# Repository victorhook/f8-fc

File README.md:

# f8 fc - Open source brushed x8 AIO

[f8 fc](https://github.com/victorhook/f8-fc) is a fully open source AIO flight controller that is made primarily for small drones with brushed drones. It features:
- STM32F405 microcontroller with 1MB flash
- BMI270 imu
- BMP388 barometer
- Onboard 16MB external flash for data logging
- Status LEDs
- 1-4s input voltage
- 4 available UARTs
- **8** brushed motor drives with 6A mosfets
- Voltage & current sensing
- Runs ardupilot

## How to flash Ardupilot
1. Get ardupilot toolchain and put the `hwdef.dat` and `hwdef_bl.dat` in `ardupilot/libraries/AP_HAL_ChibiOS/hwdef/f8-fc/`
2. Build bootloader
```
./waf clean
./waf configure --board f8-fc --bootloader
./waf bootloader
```
3. Flash bootloader using something like STM32CubeProgrammer. Hold boot button when powering on the board to boot in DFU mode.
4. Build firmware and upload using the bootloader (have board plugged in to USB and ensure you get a new serial port)
```
./waf configure --board f8-fc
./waf copter --upload
```

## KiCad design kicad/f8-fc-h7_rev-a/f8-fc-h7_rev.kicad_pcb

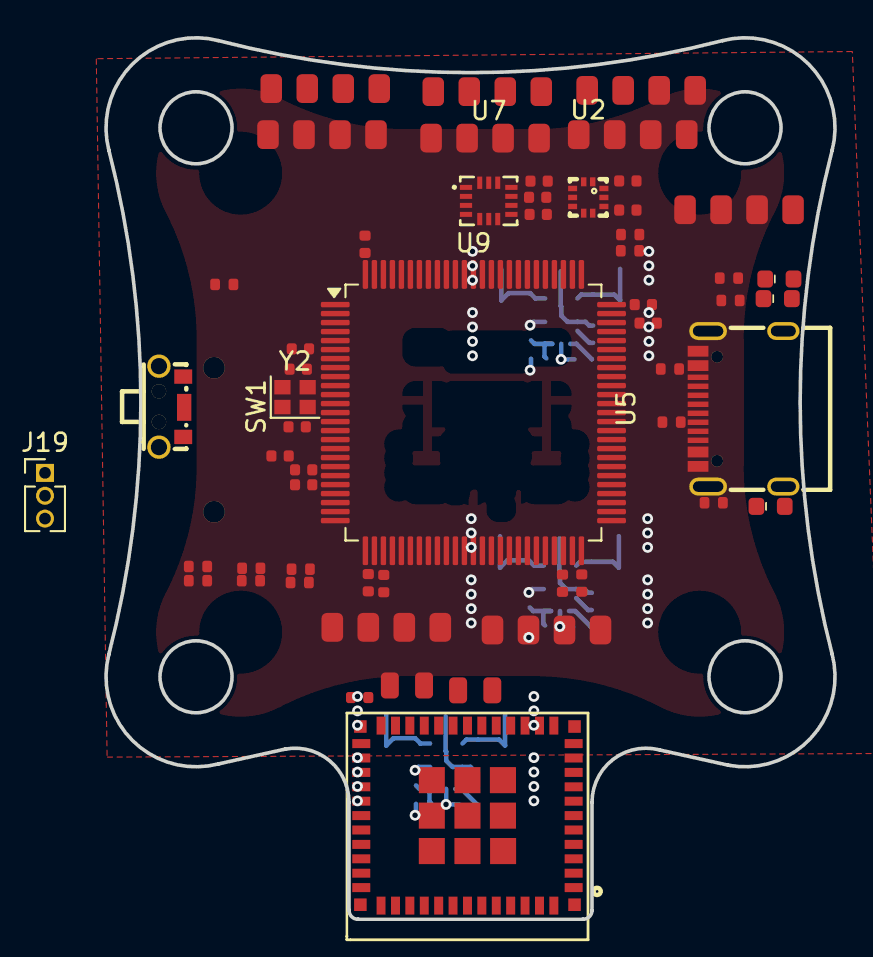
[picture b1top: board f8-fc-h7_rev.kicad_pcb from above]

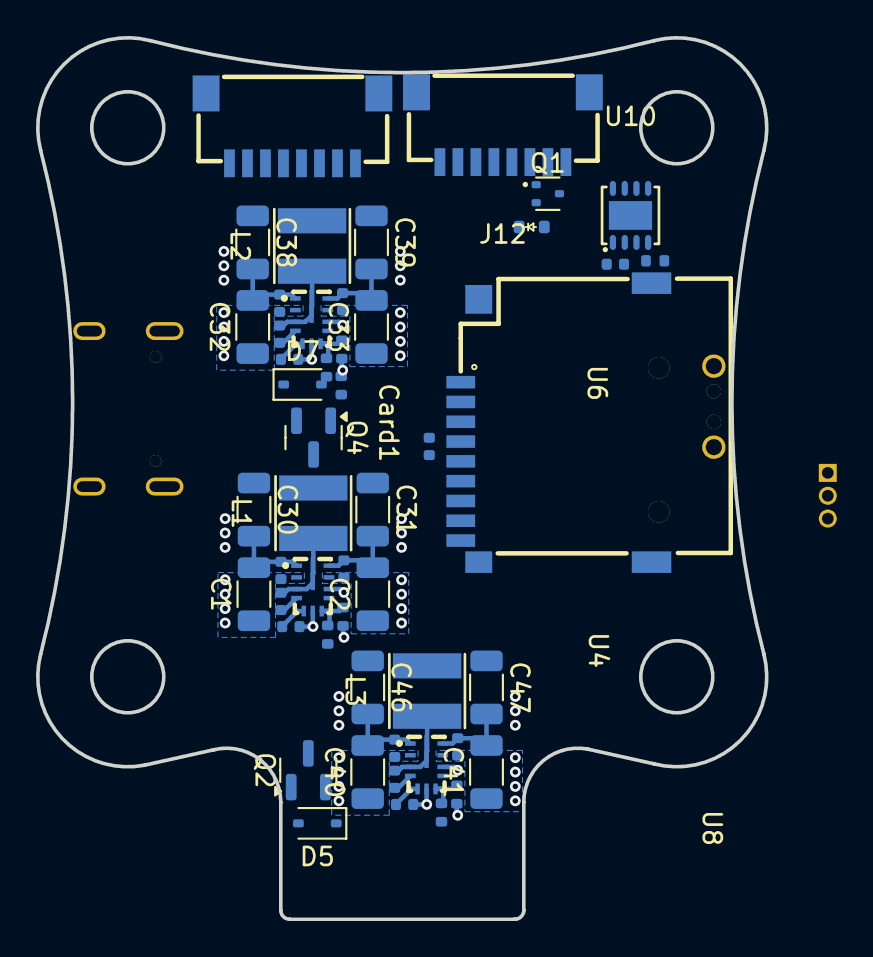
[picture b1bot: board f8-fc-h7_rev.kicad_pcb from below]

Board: 4 copper layers, 40.5 x 49.0 mm, 105 parts (50 on the bottom side), 46 nets.

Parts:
C1, C2, C32, C33, C40, C41: 10uF; C_1206_3216Metric
C3, C11: 10uF; C_0805_2012Metric_NoSilk
C4, C5, C6, C7, C9, C10, C17, C21, C22, C29, C37, C45, C48, C50, C52, C53, C54: 0.1uF; C_0402_1005Metric_NoSilk
C8: 4.7uF; C_0402_1005Metric_NoSilk
C18, C23: 15pF; C_0402_1005Metric_NoSilk
C19: 10nF; C_0402_1005Metric_NoSilk
C20, C49, C51: 2.2uF; C_0402_1005Metric_NoSilk
C24, C27, C34, C35, C42, C43: 220nF; C_0402_1005Metric_NoSilk
C28, C36, C44: 1uF; C_0402_1005Metric_NoSilk
C30, C31, C38, C39, C46, C47: 22uF; C_1206_3216Metric
Card1: TF PUSH; TF-SMD_TF-PUSH
D1: RED; LED_0603_1608Metric_NoSilk
D2: BLUE; LED_0603_1608Metric_NoSilk
D3: GREEN; LED_0603_1608Metric_NoSilk
D4: D_Schottky; D_SOD-523_NoSilk
D5, D7: D_Schottky; D_SOD-323
J1, J12: FC-ESC con; CONN-TH_SM08B-SRSS-TB-LF-SN
J10: USART1; Conn_4_Accesory_Bigger
J11: USART2; Conn_4_Accesory_Bigger
J14: UART4; Conn_4_Accesory_Bigger
J15: USART6; Conn_4_Accesory_Bigger
J16, J17, J18, J18#2, J18#3: I2C; Conn_4_Accesory_Bigger
J19: Debug; PinHeader_1x03_P1.27mm_Vertical
L1, L2, L3: 6.8uH; IND-SMD_L4.1-W4.1_ASFPIG4020
Q1: PMOS; SOT-523
Q2, Q4: WST4041; SOT-23
R1, R14, R16: 100k; R_0402_1005Metric_NoSilk
R2, R3, R11, R13, R20, R22, R23: 10k; R_0402_1005Metric_NoSilk
R4, R5, R6, R18: 1k; R_0402_1005Metric_NoSilk
R9, R10: 5.11k; R_0402_1005Metric_NoSilk
R12: 12.5K; R_0402_1005Metric_NoSilk
R15: 24.9k; R_0402_1005Metric_NoSilk
R17: 43.5k; R_0402_1005Metric_NoSilk
R24, R25: 2.2k; R_0402_1005Metric_NoSilk
R26: 120R; R_0402_1005Metric_NoSilk
SW1: SW_SPST; SW-SMD_TS-1086EV-16
U2: BMP388; SENSORM-SMD_BMP388
U3: ESP32-C3-MINI-1U-N4; WIFIM-SMD_61P-L13.2-W12.5-P0.80
U4, U6, U8: LMR33630AQRNXRQ1; VQFN-12_L3.0-W2.0-P0.65-BL_TI_RNX
U5: GT-USB-7010AN; USB-SMD_GT-USB-7010AN
U7: ICM-42688-P; LGA-14_L3.0-W2.5-P0.50-TL
U9: STM32H743VIT6; LQFP-100_14x14mm_P0.5mm
U10: SIT1050TK; TDFN-8_L3.0-W3.0-P0.65-BL-EP
Y2: 16 MHz; Crystal_SMD_2016-4Pin_2.0x1.6mm

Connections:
+3.3V: C3.1, C4.1, C5.1, C6.1, C8.1, C9.1, C10.1, C11.1, C17.1, C19.1, C20.1, C21.1, C22.1, C48.1, C50.1, C52.1, C53.1, C54.1, Card1.4 (VDD), J16.3, SW1.2 (B), U2.1 (VDDIO), U2.6 (CSB), U2.10 (VDD), U3.3 (3V3), U7.5 (VDDIO), U7.8 (VDD), U9.6 (VBAT), U9.11 (VDD), U9.20 (VREF+), U9.21 (VDDA), U9.27 (VDD), U9.50 (VDD), U9.75 (VDD), U9.100 (VDD), U10.5 (Vref)
+3V3: C46.1, C47.1, L3.2, R16.1, R24.1, R25.1
+4V5: C7.1, D7.1 (K), Q4.2 (S), U10.3 (VCC)
+5V: C30.1, C31.1, L1.2, Q4.3 (D), R1.1
+9V: C38.1, C39.1, L2.2, R14.1
BOOT0: R13.1, SW1.1 (A), U9.94 (BOOT0)
CANH: R26.1, U10.7 (CANH)
CANL: R26.2, U10.6 (CANL)
CURR_EXT: J1.3, J12.3
CURR_SENSE: R22.2, R23.1
GND: C1.2, C2.2, C3.2, C4.2, C5.2, C6.2, C7.2, C8.2, C9.2, C10.2, C11.2, C17.2, C18.2, C19.2, C20.2, C21.2, C22.2, C23.2, C24.2, C27.2, C28.1, C30.2, C31.2, C32.2, C33.2, C34.2, C35.2, C36.1, C38.2, C39.2, C40.2, C41.2, C42.2, C43.2, C44.1, C46.2, C47.2, C48.2, C49.2, C50.2, C51.2, C52.2, C53.2, C54.2, Card1.6 (VSS), D1.1 (K), D2.1 (K), D3.1 (K), J1.2, J10.4, J11.4, J12.2, J14.4, J15.4, J16.4, J17.4, J18.4, J18#2.4, J18#3.4, J19.3, R3.2, R9.2, R10.2, R12.2, R13.2, R15.2, R17.2, R18.2, R20.2, R23.2, U2.3 (VSS), U2.5 (SDO), U2.8 (VSS), U2.9 (VSS), U3.1 (GND), U3.2 (GND), U3.11 (GND), U3.14 (GND), U3.36 (GND), U3.37 (GND), U3.38 (GND), U3.39 (GND), U3.40 (GND), U3.41 (GND), U3.42 (GND), U3.43 (GND), U3.44 (GND), U3.45 (GND), U3.46 (GND), U3.47 (GND), U3.48 (GND), U3.49 (GND), U3.50 (GND), U3.51 (GND), U3.52 (GND), U3.53 (GND), U3.54 (GND), U3.55 (GND), U3.56 (GND), U3.57 (GND), U3.58 (GND), U3.59 (GND), U3.60 (GND), U3.61 (GND), U4.1 (PGND), U4.6 (AGND), U4.11 (PGND), U5.13 (GND), U5.14 (GND), U5.15 (GND), U5.16 (GND), U5.A1B12 (GND), U5.B1A12 (GND), U6.1 (PGND), U6.6 (AGND), U6.11 (PGND), U7.6 (GND), U8.1 (PGND), U8.6 (AGND), U8.11 (PGND), U9.10 (VSS), U9.19 (VSSA), U9.26 (VSS), U9.49 (VSS), U9.74 (VSS), U9.99 (VSS), U10.2 (GND), U10.8 (S), U10.9 (EP), Y2.2, Y2.4
I2C1_SCL: J16.2, R25.2, U2.2 (SCK)
I2C1_SDA: J16.1, R24.2, U2.4 (SDI)
unnamed: C49.1, U9.48 (VCAP)
unnamed: C51.1, U9.73 (VCAP)
unnamed: D1.2 (A), R4.1
unnamed: D2.2 (A), R5.1
unnamed: D3.2 (A), R6.1
unnamed: C29.1, U4.4 (BOOT)
unnamed: R1.2, R12.1, U4.7 (FB)
unnamed: C29.2, L1.1, U4.3 (NC), U4.12 (SW)
unnamed: C28.2, U4.5 (VCC)
unnamed: R10.1, U5.A5 (CC1)
unnamed: R9.1, U5.B5 (CC2)
unnamed: C37.1, U6.4 (BOOT)
unnamed: R14.2, R15.1, U6.7 (FB)
unnamed: C37.2, L2.1, U6.3 (NC), U6.12 (SW)
unnamed: C36.2, U6.5 (VCC)
unnamed: C45.1, U8.4 (BOOT)
unnamed: R16.2, R17.1, U8.7 (FB)
unnamed: C45.2, L3.1, U8.3 (NC), U8.12 (SW)
unnamed: C44.2, U8.5 (VCC)
unnamed: C18.1, U9.12 (PH0), Y2.1
unnamed: C23.1, U9.13 (PH1), Y2.3
RGB_LED: J18.1, J18#2.1, J18#3.1
SERVO_3: J18.2, J18#2.2, J18#3.2
SWCLK: J19.1, U9.76 (PA14)
SWDIO: J19.2, U9.72 (PA13)
Telemetry: J1.4, J12.4
USB+: U5.A6 (DP1), U5.B6 (DP2), U9.71 (PA12)
USB-: U5.A7 (DN1), U5.B7 (DN2), U9.70 (PA11)
VBAT: C1.1, C2.1, C24.1, C27.1, C32.1, C33.1, C34.1, C35.1, J1.1, J10.3, J11.3, J12.1, J14.3, J15.3, J17.3, J18.3, J18#2.3, J18#3.3, Q1.3 (D), R11.1, U4.2 (VIN), U4.9 (EN), U4.10 (VIN), U6.2 (VIN), U6.9 (EN), U6.10 (VIN)
VBAT_SENSE: R11.2, R18.1
VBUS: D4.2 (A), D5.2 (A), D7.2 (A), Q1.1 (G), Q4.1 (G), R2.1, R20.1, U5.A4B9 (VBUS), U5.B4A9 (VBUS)
VSUB_SENSE: R2.2, R3.1, U9.68 (PA9)
VSYS: C40.1, C41.1, C42.1, C43.1, D4.1 (K), D5.1 (K), Q1.2 (S), U8.2 (VIN), U8.9 (EN), U8.10 (VIN)

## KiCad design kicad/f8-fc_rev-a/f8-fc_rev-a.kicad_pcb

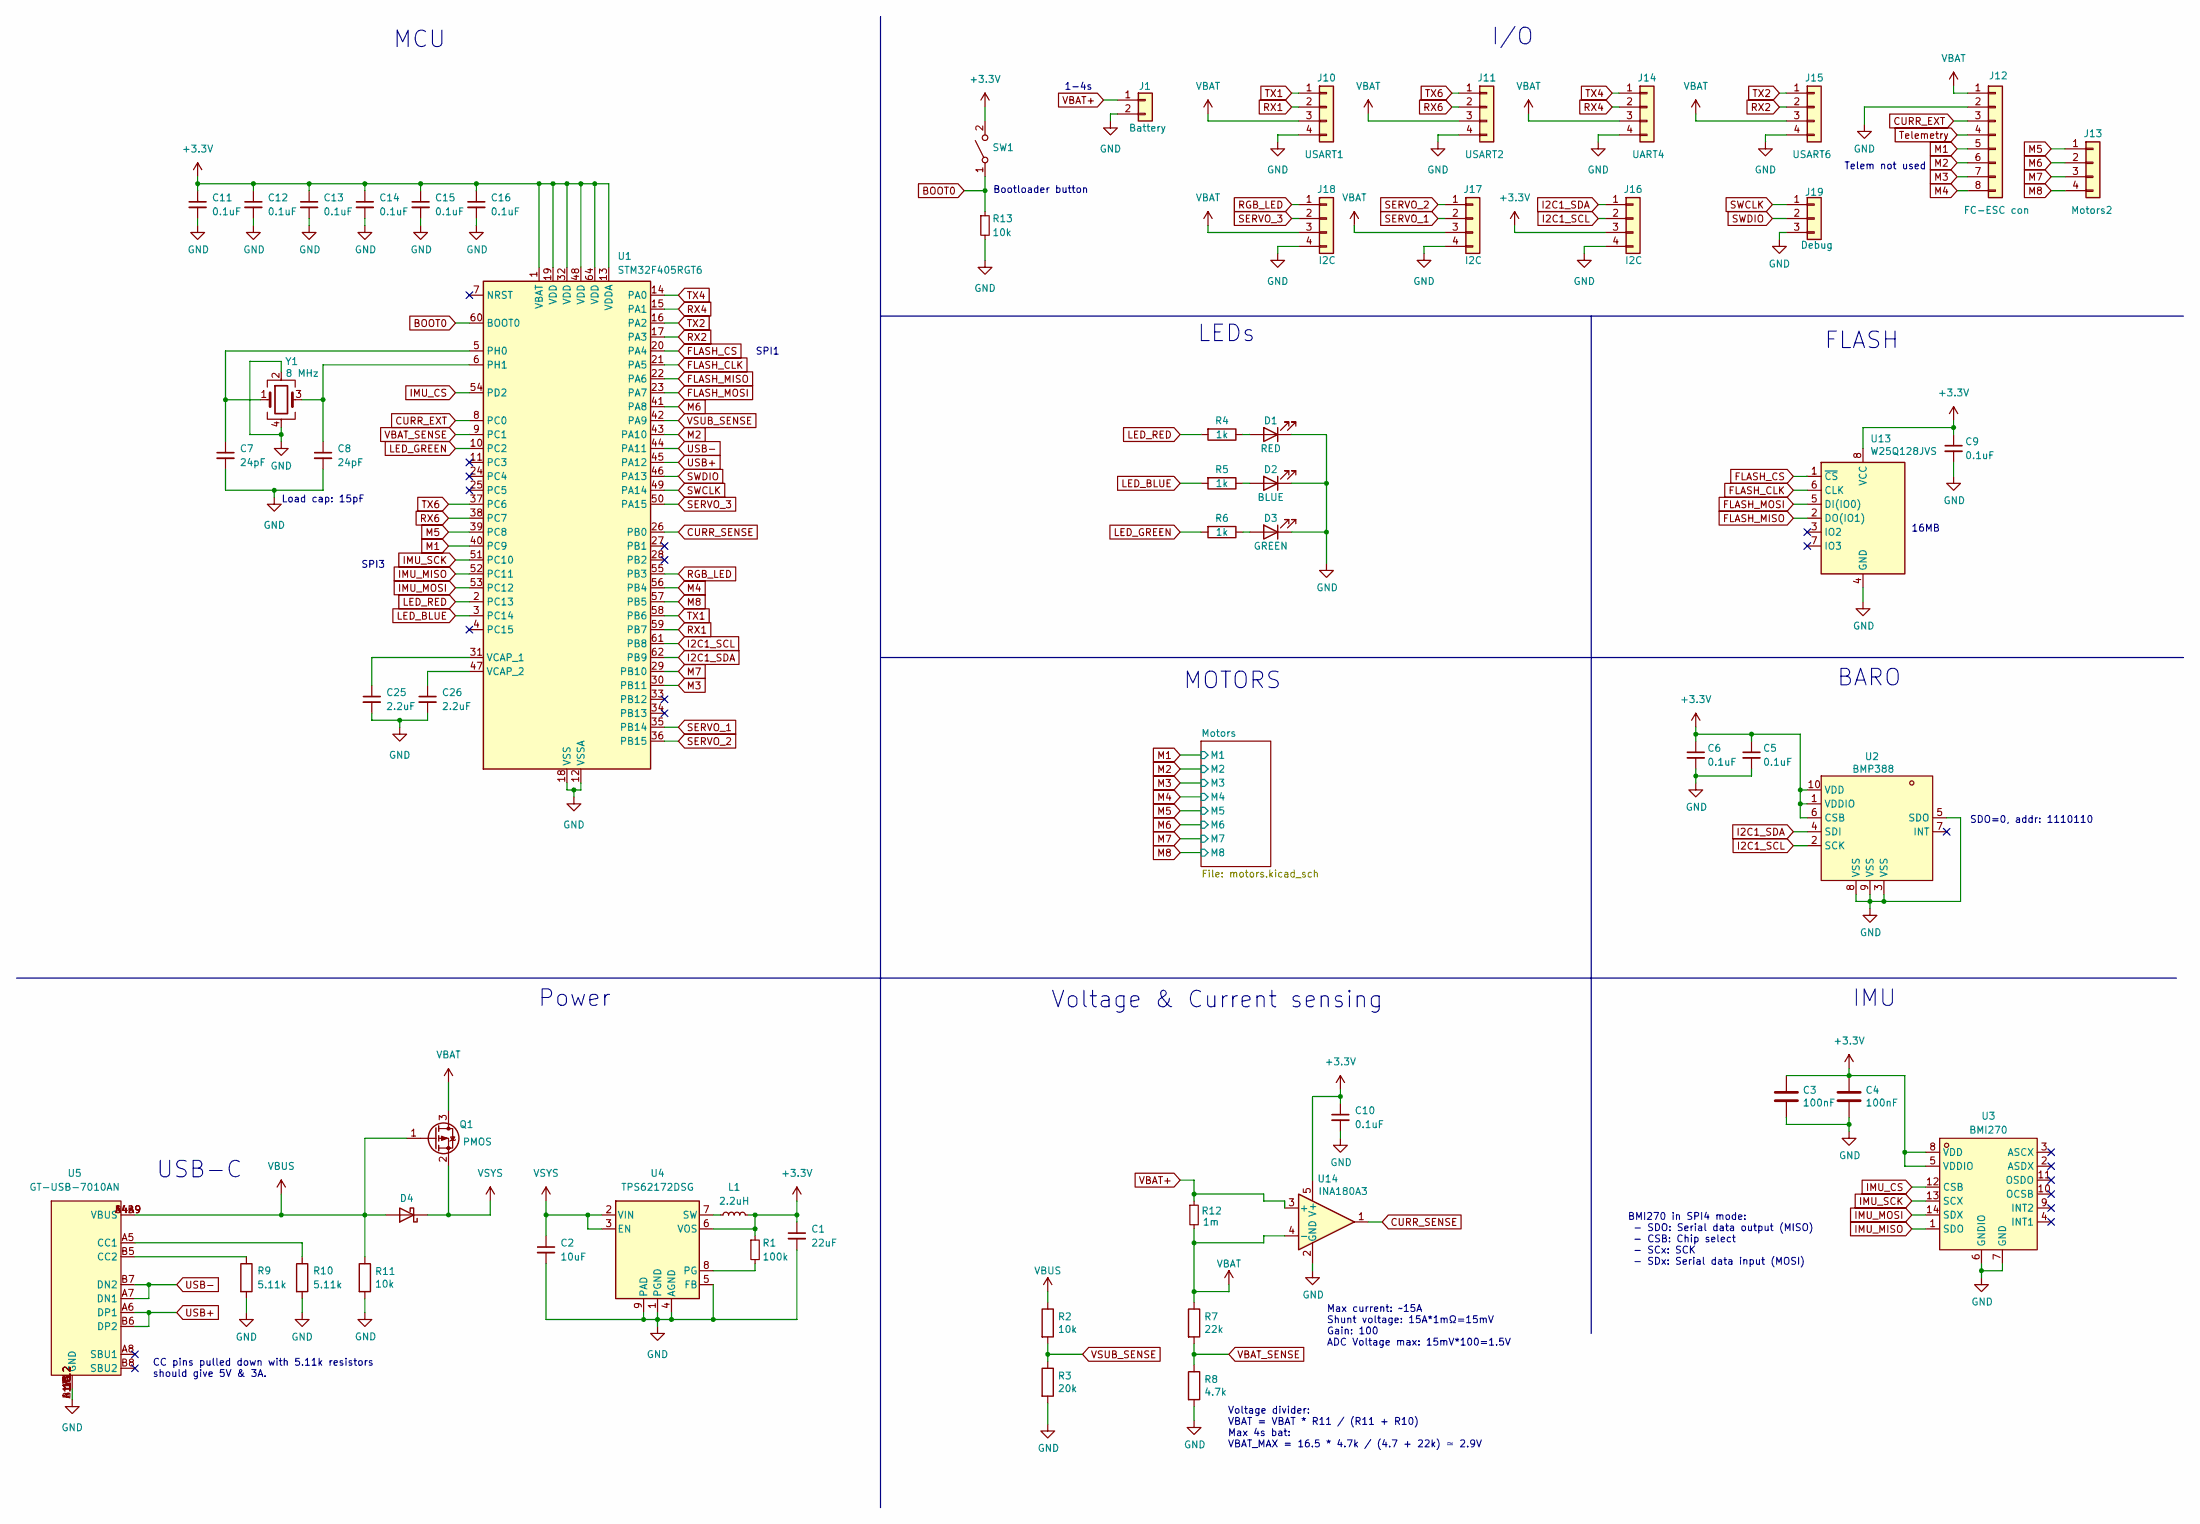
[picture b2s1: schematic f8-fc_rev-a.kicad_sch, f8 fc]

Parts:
C1: 22uF; C_0603_1608Metric_NoSilk
C2: 10uF; C_0603_1608Metric_NoSilk
C3, C4: 100nF; C_0402_1005Metric_NoSilk
C5, C6, C9, C10, C11, C12, C13, C14, C15, C16: 0.1uF; C_0402_1005Metric_NoSilk
C7, C8: 24pF; C_0402_1005Metric_NoSilk
C25, C26: 2.2uF; C_0402_1005Metric_NoSilk
D1: RED; LED_0603_1608Metric_NoSilk
D2: BLUE; LED_0603_1608Metric_NoSilk
D3: GREEN; LED_0603_1608Metric_NoSilk
D4: D_Schottky; D_SOD-523_NoSilk; LCSC Part C455040
J1: Battery; Conn_2_Bat
J10: USART1; Conn_4_Accesory
J11: USART2; Conn_4_Accesory
J12: FC-ESC con; Conn_8_Accesory
J13: Motors2; Conn_4_Accesory
J14: UART4; Conn_4_Accesory
J15: USART6; Conn_4_Accesory
J16, J17, J18: I2C; Conn_4_Accesory
J19: Debug; PinHeader_1x03_P1.27mm_Vertical
L1: 2.2uH; L_0402_1005Metric
Q1: PMOS; SOT-523; LCSC Part C5334586
R1: 100k; R_0402_1005Metric_NoSilk
R2, R11, R13: 10k; R_0402_1005Metric_NoSilk
R3: 20k; R_0402_1005Metric_NoSilk
R4, R5, R6: 1k; R_0402_1005Metric_NoSilk
R7: 22k; R_0402_1005Metric_NoSilk
R8: 4.7k; R_0402_1005Metric_NoSilk
R9, R10: 5.11k; R_0402_1005Metric_NoSilk
R12: 1m; R_1206_3216Metric; LCSC Part C7419993
SW1: SW_SPST; SW-SMD_TS-1086EV-16
U1: STM32F405RGT6; LQFP-64_10x10mm_P0.5mm
U2: BMP388; SENSORM-SMD_BMP388; LCSC Part C779278
U3: BMI270; LGA-14_L3.0-W2.5-P0.50-BR; LCSC Part C2836813
U4: TPS62172DSG; WSON-8-1EP_2x2mm_P0.5mm_EP0.9x1.6mm_ThermalVias
U5: GT-USB-7010AN; USB-SMD_GT-USB-7010AN; LCSC Part C963370
U13: W25Q128JVS; SOIC-8_5.23x5.23mm_P1.27mm; LCSC Part C97521
U14: INA180A3; SOT-23-5; LCSC Part C122882
Y1: 8 MHz; Crystal_SMD_2016-4Pin_2.0x1.6mm; LCSC Part C2831375

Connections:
+3.3V: C1.1, C3.1, C4.1, C5.1, C6.1, C9.1, C10.1, C11.1, C12.1, C13.1, C14.1, C15.1, C16.1, J16.3, L1.2, R1.1, SW1.2 (B), U1.1 (VBAT), U1.13 (VDDA), U1.19 (VDD), U1.32 (VDD), U1.48 (VDD), U1.64 (VDD), U2.1 (VDDIO), U2.6 (CSB), U2.10 (VDD), U3.5 (VDDIO), U3.8 (VDD), U4.6 (VOS), U13.8 (VCC), U14.5 (V+)
BOOT0: R13.1, SW1.1 (A), U1.60 (BOOT0)
CURR_EXT: J12.3, U1.8 (PC0)
CURR_SENSE: U1.26 (PB0), U14.1
FLASH_CLK: U1.21 (PA5), U13.6 (CLK)
FLASH_CS: U1.20 (PA4), U13.1 (~CS)
FLASH_MISO: U1.22 (PA6), U13.2 (DO(IO1))
FLASH_MOSI: U1.23 (PA7), U13.5 (DI(IO0))
GND: C1.2, C2.2, C3.2, C4.2, C5.2, C6.2, C7.2, C8.2, C9.2, C10.2, C11.2, C12.2, C13.2, C14.2, C15.2, C16.2, C25.2, C26.2, D1.1 (K), D2.1 (K), D3.1 (K), J1.2, J10.4, J11.4, J12.2, J14.4, J15.4, J16.4, J17.4, J18.4, J19.3, R3.2, R8.2, R9.2, R10.2, R11.2, R13.2, U1.12 (VSSA), U1.18 (VSS), U1.63 (VSS), U2.3 (VSS), U2.5 (SDO), U2.8 (VSS), U2.9 (VSS), U3.6 (GNDIO), U3.7 (GND), U4.1 (PGND), U4.4 (AGND), U4.5 (FB), U4.9 (PAD), U5.13 (GND), U5.14 (GND), U5.15 (GND), U5.16 (GND), U5.A1B12 (GND), U5.B1A12 (GND), U13.4 (GND), U14.2 (GND), Y1.2, Y1.4; also elsewhere on the board
I2C1_SCL: J16.2, U1.61 (PB8), U2.2 (SCK)
I2C1_SDA: J16.1, U1.62 (PB9), U2.4 (SDI)
IMU_CS: U1.54 (PD2), U3.12 (CSB)
IMU_MISO: U1.52 (PC11), U3.1 (SDO)
IMU_MOSI: U1.53 (PC12), U3.14 (SDX)
IMU_SCK: U1.51 (PC10), U3.13 (SCX)
LED_BLUE: R5.2, U1.3 (PC14)
LED_GREEN: R6.2, U1.10 (PC2)
LED_RED: R4.2, U1.2 (PC13)
M1: J12.5, U1.40 (PC9); also elsewhere on the board
M2: J12.6, U1.43 (PA10); also elsewhere on the board
M3: J12.7, U1.30 (PB11); also elsewhere on the board
M4: J12.8, U1.56 (PB4); also elsewhere on the board
M5: J13.1, U1.39 (PC8); also elsewhere on the board
M6: J13.2, U1.41 (PA8); also elsewhere on the board
M7: J13.3, U1.29 (PB10); also elsewhere on the board
M8: J13.4, U1.57 (PB5); also elsewhere on the board
unnamed: D1.2 (A), R4.1
unnamed: D2.2 (A), R5.1
unnamed: D3.2 (A), R6.1
unnamed: C7.1, U1.5 (PH0), Y1.1
unnamed: C8.1, U1.6 (PH1), Y1.3
unnamed: C25.1, U1.31 (VCAP_1)
unnamed: C26.1, U1.47 (VCAP_2)
unnamed: R1.2, U4.8 (PG)
unnamed: L1.1, U4.7 (SW)
unnamed: R10.1, U5.A5 (CC1)
unnamed: R9.1, U5.B5 (CC2)
RGB_LED: J18.1, U1.55 (PB3)
RX1: J10.2, U1.59 (PB7)
RX2: J15.2, U1.17 (PA3)
RX4: J14.2, U1.15 (PA1)
RX6: J11.2, U1.38 (PC7)
SERVO_1: J17.2, U1.35 (PB14)
SERVO_2: J17.1, U1.36 (PB15)
SERVO_3: J18.2, U1.50 (PA15)
SWCLK: J19.1, U1.49 (PA14)
SWDIO: J19.2, U1.46 (PA13)
TX1: J10.1, U1.58 (PB6)
TX2: J15.1, U1.16 (PA2)
TX4: J14.1, U1.14 (PA0)
TX6: J11.1, U1.37 (PC6)
Telemetry: J12.4
USB+: U1.45 (PA12), U5.A6 (DP1), U5.B6 (DP2)
USB-: U1.44 (PA11), U5.A7 (DN1), U5.B7 (DN2)
VBAT: J10.3, J11.3, J12.1, J14.3, J15.3, J17.3, J18.3, Q1.3 (D), R7.1, R12.2, U14.4 (-); also elsewhere on the board
VBAT+: J1.1, R12.1, U14.3 (+)
VBAT_SENSE: R7.2, R8.1, U1.9 (PC1)
VBUS: D4.2 (A), Q1.1 (G), R2.1, R11.1, U5.A4B9 (VBUS), U5.B4A9 (VBUS)
VSUB_SENSE: R2.2, R3.1, U1.42 (PA9)
VSYS: C2.1, D4.1 (K), Q1.2 (S), U4.2 (VIN), U4.3 (EN)

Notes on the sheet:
Max current: ~15A Shunt voltage: 15A*1mΩ=15mV Gain: 100 ADC Voltage max: 15mV*100=1.5V
MCU
SDO=0, addr: 1110110
BMI270 in SPI4 mode: - SDO: Serial data output (MISO) - CSB: Chip select - SCx: SCK - SDx: Serial data input (MOSI)
16MB
Telem not used
Voltage & Current sensing
LEDs
FLASH
IMU
I/O
CC pins pulled down with 5.11k resistors should give 5V & 3A.
Bootloader button
BARO
Load cap: 15pF
Voltage divider: VBAT = VBAT * R11 / (R11 + R10) Max 4s bat: VBAT_MAX = 16.5 * 4.7k / (4.7 + 22k) ≃ 2.9V
Power
SPI3
USB-C
SPI1
1-4s
MOTORS

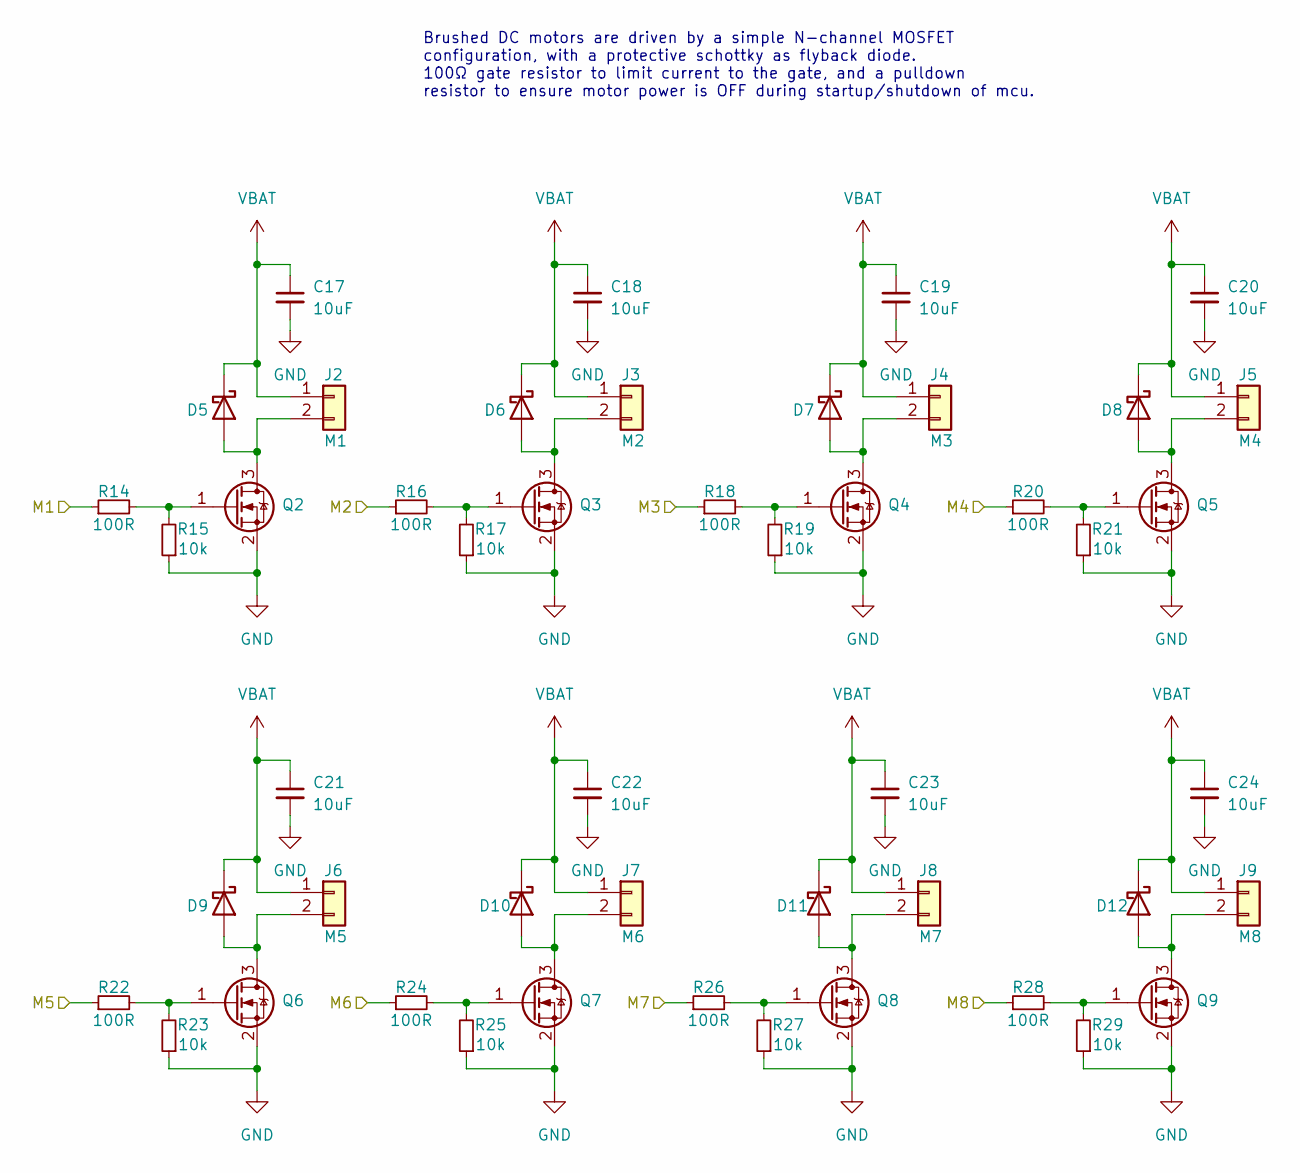
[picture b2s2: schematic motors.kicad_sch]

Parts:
C17, C18, C19, C20, C21, C22, C23, C24: 10uF; C_0402_1005Metric_NoSilk
D5, D6, D7, D8, D9, D10, D11, D12: D_Schottky; D_SOD-523_NoSilk; LCSC Part C455040
J2: M1; Conn_2_Motors
J3: M2; Conn_2_Motors
J4: M3; Conn_2_Motors
J5: M4; Conn_2_Motors
J6: M5; Conn_2_Motors
J7: M6; Conn_2_Motors
J8: M7; Conn_2_Motors
J9: M8; Conn_2_Motors
Q2, Q3, Q4, Q5, Q6, Q7, Q8, Q9: 2300A; SOT-23_NoSilk; LCSC Part C7437077
R14, R16, R18, R20, R22, R24, R26, R28: 100R; R_0402_1005Metric_NoSilk
R15, R17, R19, R21, R23, R25, R27, R29: 10k; R_0402_1005Metric_NoSilk

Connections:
GND: C17.2, C18.2, C19.2, C20.2, C21.2, C22.2, C23.2, C24.2, Q2.2 (S), Q3.2 (S), Q4.2 (S), Q5.2 (S), Q6.2 (S), Q7.2 (S), Q8.2 (S), Q9.2 (S), R15.1, R17.1, R19.1, R21.1, R23.1, R25.1, R27.1, R29.1; also elsewhere on the board
M1: R14.1; also elsewhere on the board
M2: R16.1; also elsewhere on the board
M3: R18.1; also elsewhere on the board
M4: R20.1; also elsewhere on the board
M5: R22.1; also elsewhere on the board
M6: R24.1; also elsewhere on the board
M7: R26.1; also elsewhere on the board
M8: R28.1; also elsewhere on the board
unnamed: D5.2 (A), J2.2, Q2.3 (D)
unnamed: D6.2 (A), J3.2, Q3.3 (D)
unnamed: D7.2 (A), J4.2, Q4.3 (D)
unnamed: D8.2 (A), J5.2, Q5.3 (D)
unnamed: D9.2 (A), J6.2, Q6.3 (D)
unnamed: D10.2 (A), J7.2, Q7.3 (D)
unnamed: D11.2 (A), J8.2, Q8.3 (D)
unnamed: D12.2 (A), J9.2, Q9.3 (D)
unnamed: Q2.1 (G), R14.2, R15.2
unnamed: Q3.1 (G), R16.2, R17.2
unnamed: Q4.1 (G), R18.2, R19.2
unnamed: Q5.1 (G), R20.2, R21.2
unnamed: Q6.1 (G), R22.2, R23.2
unnamed: Q7.1 (G), R24.2, R25.2
unnamed: Q8.1 (G), R26.2, R27.2
unnamed: Q9.1 (G), R28.2, R29.2
VBAT: C17.1, C18.1, C19.1, C20.1, C21.1, C22.1, C23.1, C24.1, D5.1 (K), D6.1 (K), D7.1 (K), D8.1 (K), D9.1 (K), D10.1 (K), D11.1 (K), D12.1 (K), J2.1, J3.1, J4.1, J5.1, J6.1, J7.1, J8.1, J9.1; also elsewhere on the board

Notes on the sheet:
Brushed DC motors are driven by a simple N-channel MOSFET configuration, with a protective schottky as flyback diode. 100Ω gate resistor to limit current to the gate, and a pulldown resistor to ensure motor power is OFF during startup/shutdown of mcu.

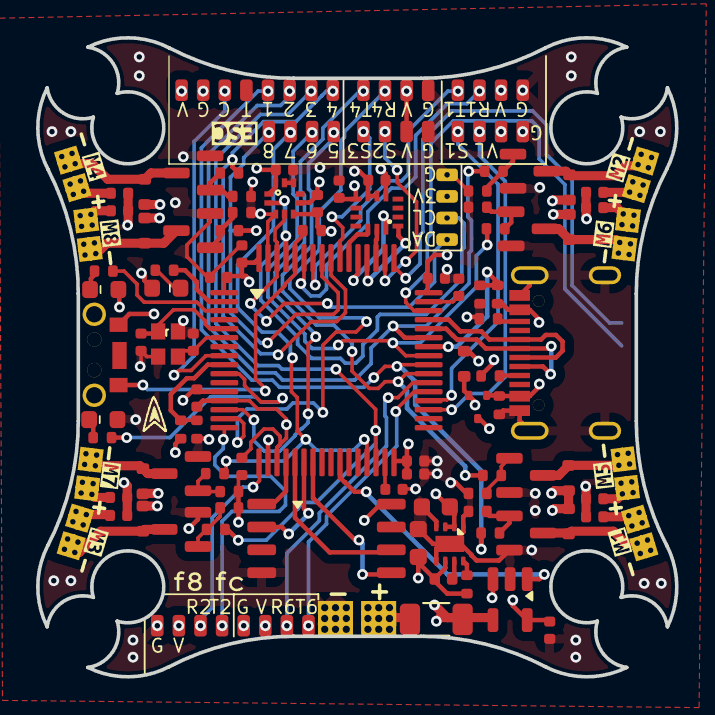
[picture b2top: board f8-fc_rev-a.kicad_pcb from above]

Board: 4 copper layers, 35.5 x 35.5 mm, 114 parts (1 on the bottom side), 75 nets.

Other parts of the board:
kibuzzard-66DD79C8: G***; kibuzzard-66DD79C8
kibuzzard-66DD79DA: G***; kibuzzard-66DD79DA
kibuzzard-66DD778E: G***; kibuzzard-66DD778E
kibuzzard-66DD7786: G***; kibuzzard-66DD7786
kibuzzard-66E556E1: G***; kibuzzard-66E556E1
kibuzzard-66E556E7: G***; kibuzzard-66E556E7
kibuzzard-66E3374B: G***; kibuzzard-66E3374B
kibuzzard-66E5570F: G***; kibuzzard-66E5570F
kibuzzard-66E55715: G***; kibuzzard-66E55715

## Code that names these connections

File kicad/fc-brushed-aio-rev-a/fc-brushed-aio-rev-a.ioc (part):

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Mcu.Name=STM32F405RGTx
Mcu.Package=LQFP64
Mcu.UserName=STM32F405RGTx
PA0-WKUP.Signal=UART4_TX
PA1.Signal=UART4_RX
PA10.GPIOParameters=GPIO_Label
PA10.GPIO_Label=M2
PA10.Signal=S_TIM1_CH3
PA11.Signal=USB_OTG_FS_DM
PA12.Signal=USB_OTG_FS_DP
PA13.Signal=SYS_JTMS-SWDIO
PA14.Signal=SYS_JTCK-SWCLK
PA15.GPIOParameters=GPIO_Label
PA15.GPIO_Label=S2
PA15.Signal=S_TIM2_CH1_ETR
PA2.Signal=USART2_TX
PA3.Signal=USART2_RX
PA4.GPIOParameters=GPIO_Label
PA4.GPIO_Label=FLASH_CS
PA4.Signal=SPI1_NSS
PA5.GPIOParameters=GPIO_Label
PA5.GPIO_Label=FLASH_SCK
PA5.Signal=SPI1_SCK
PA6.GPIOParameters=GPIO_Label
PA6.GPIO_Label=FLASH_MISO
PA6.Signal=SPI1_MISO
PA7.GPIOParameters=GPIO_Label
PA7.GPIO_Label=FLASH_MOSI
PA7.Signal=SPI1_MOSI
PA8.GPIOParameters=GPIO_Label
PA8.GPIO_Label=M6
PA8.Signal=S_TIM1_CH1
PA9.Signal=USB_OTG_FS_VBUS
PB0.GPIOParameters=GPIO_Label
PB0.GPIO_Label=CURRENT_SENSE
PB0.Signal=ADCx_IN8
PB10.GPIOParameters=GPIO_Label
PB10.GPIO_Label=M7
PB10.Signal=S_TIM2_CH3
PB11.GPIOParameters=GPIO_Label
PB11.GPIO_Label=M3
PB11.Signal=S_TIM2_CH4
PB14.GPIOParameters=GPIO_Label
PB14.GPIO_Label=RGB_LED
PB14.Signal=S_TIM12_CH1
PB15.GPIOParameters=GPIO_Label
PB15.GPIO_Label=S1
PB15.Signal=S_TIM12_CH2
PB3.GPIOParameters=GPIO_Label
PB3.GPIO_Label=S3
PB3.Signal=S_TIM2_CH2
PB4.GPIOParameters=GPIO_Label
PB4.GPIO_Label=M4
PB4.Signal=S_TIM3_CH1
PB5.GPIOParameters=GPIO_Label
PB5.GPIO_Label=M8
PB5.Signal=S_TIM3_CH2
PB6.Signal=USART1_TX
PB7.Signal=USART1_RX
PB8.Signal=I2C1_SCL
PB9.Signal=I2C1_SDA
PC0.GPIOParameters=GPIO_Label
PC0.GPIO_Label=CURR_EXT
PC0.Signal=ADCx_IN10
PC1.GPIOParameters=GPIO_Label
PC1.GPIO_Label=VBAT_SENSE
PC1.Signal=ADCx_IN11
PC10.GPIOParameters=GPIO_Label
PC10.GPIO_Label=IMU_SCK
PC10.Signal=SPI3_SCK
PC11.GPIOParameters=GPIO_Label
PC11.GPIO_Label=IMU_MISO
PC11.Signal=SPI3_MISO
PC12.GPIOParameters=GPIO_Label
PC12.GPIO_Label=IMU_MOSI
PC12.Signal=SPI3_MOSI
PC13-ANTI_TAMP.GPIOParameters=GPIO_Label
PC13-ANTI_TAMP.GPIO_Label=LED_RED
PC13-ANTI_TAMP.Signal=GPIO_Output
PC14-OSC32_IN.GPIOParameters=GPIO_Label
PC14-OSC32_IN.GPIO_Label=LED_BLUE
PC14-OSC32_IN.Signal=GPIO_Output
PC2.GPIOParameters=GPIO_Label
PC2.GPIO_Label=LED_GREEN
PC2.Signal=GPIO_Output
PC6.Signal=USART6_TX
PC7.Signal=USART6_RX
PC8.GPIOParameters=GPIO_Label
PC8.GPIO_Label=M5
PC8.Signal=S_TIM3_CH3
PC9.GPIOParameters=GPIO_Label
PC9.GPIO_Label=M1
PC9.Signal=S_TIM3_CH4
PD2.GPIOParameters=GPIO_Label
PD2.GPIO_Label=IMU_CS
PD2.Signal=GPIO_Output
PH0-OSC_IN.Signal=RCC_OSC_IN
PH1-OSC_OUT.Signal=RCC_OSC_OUT
RCC.HSE_VALUE=25000000
RCC.SYSCLKFreq_VALUE=16000000
board=custom

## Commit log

2024-09-10 Added cubeMX ioc file. Not done yet
2024-09-10 Startred AP `hwdef` files
2024-09-12 More progress on pcb!
2024-09-14 Majority of routing complete. Schematic too.
2024-09-14 Got `hwdet.dat` file mostly complete. Can compile everything now
2024-09-15 Almost done with pcb! Need final checks and some silkscreen design stuff
2024-09-15 Renamed project to "f8 fc"
2024-09-15 Added some silkscreen
2024-09-15 Clenaup: Almost ready for order
    Need to get the 30.5x30.5 holes into the outline as well, otherwise all looks good
2024-09-16 Updated some AP hwdef param stuff Was able to build fw with lua scripting enabled! Under 1MB!
2024-09-18 rev. A is ready to order!
2024-09-18 Updated cap to 0603 (C2) and driver caps from 10uf to 1uf. This is because these needs to tolerate higher voltages than 10V and that isn't available at 0402 10uF..
2024-12-02 Added updated ardupilot parameter files
2024-12-02 Added AP bootloader
2024-12-02 Added readme for AP
2024-12-02 Added readme to front page
2025-02-05 Started on new board with h743 mcu
2025-02-08 Initial ethernet PHY support
    Realized however that the IC chosen (DP83848TSQ/NOPB) which
    pixhawk uses in their example in Bus standard 6, isn't supported by Ardupilot.
    So should probably change IC
2025-02-09 Swapped to LAN8742 Ethernet PHY
    This was is supported by AP so seems more safe
    to use this.
    Also seems a bit simpler in wiring as it has a few less pins.
    A downside is that I cannot find a proper application
    schematic example online..
